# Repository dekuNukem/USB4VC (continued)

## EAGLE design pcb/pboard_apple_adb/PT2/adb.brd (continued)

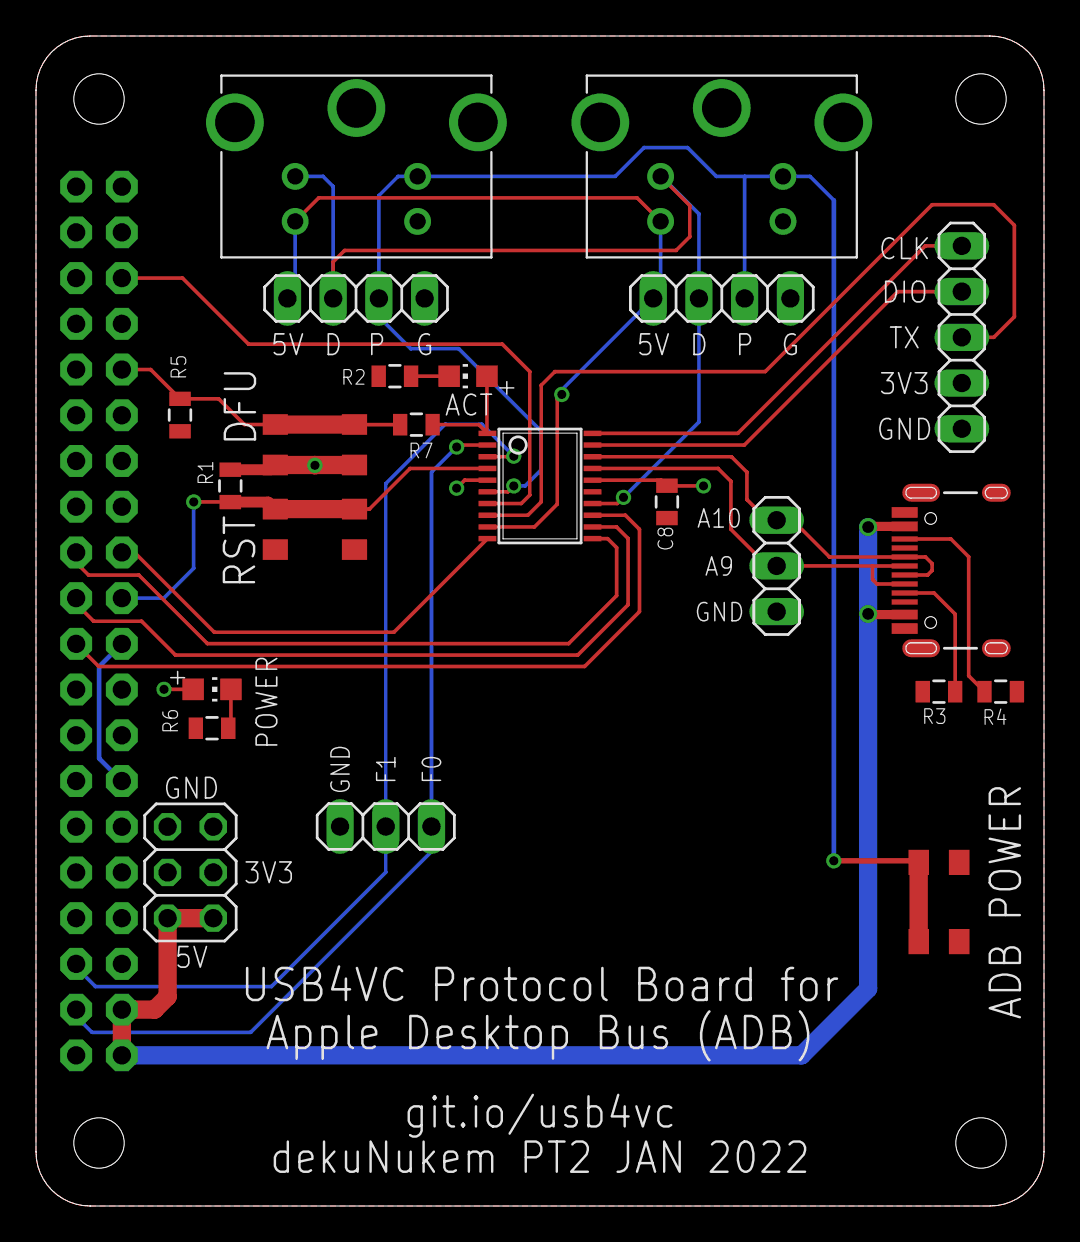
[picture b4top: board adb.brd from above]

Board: 2 copper layers, 56.0 x 65.0 mm, 28 parts (1 on the bottom side), 25 nets.

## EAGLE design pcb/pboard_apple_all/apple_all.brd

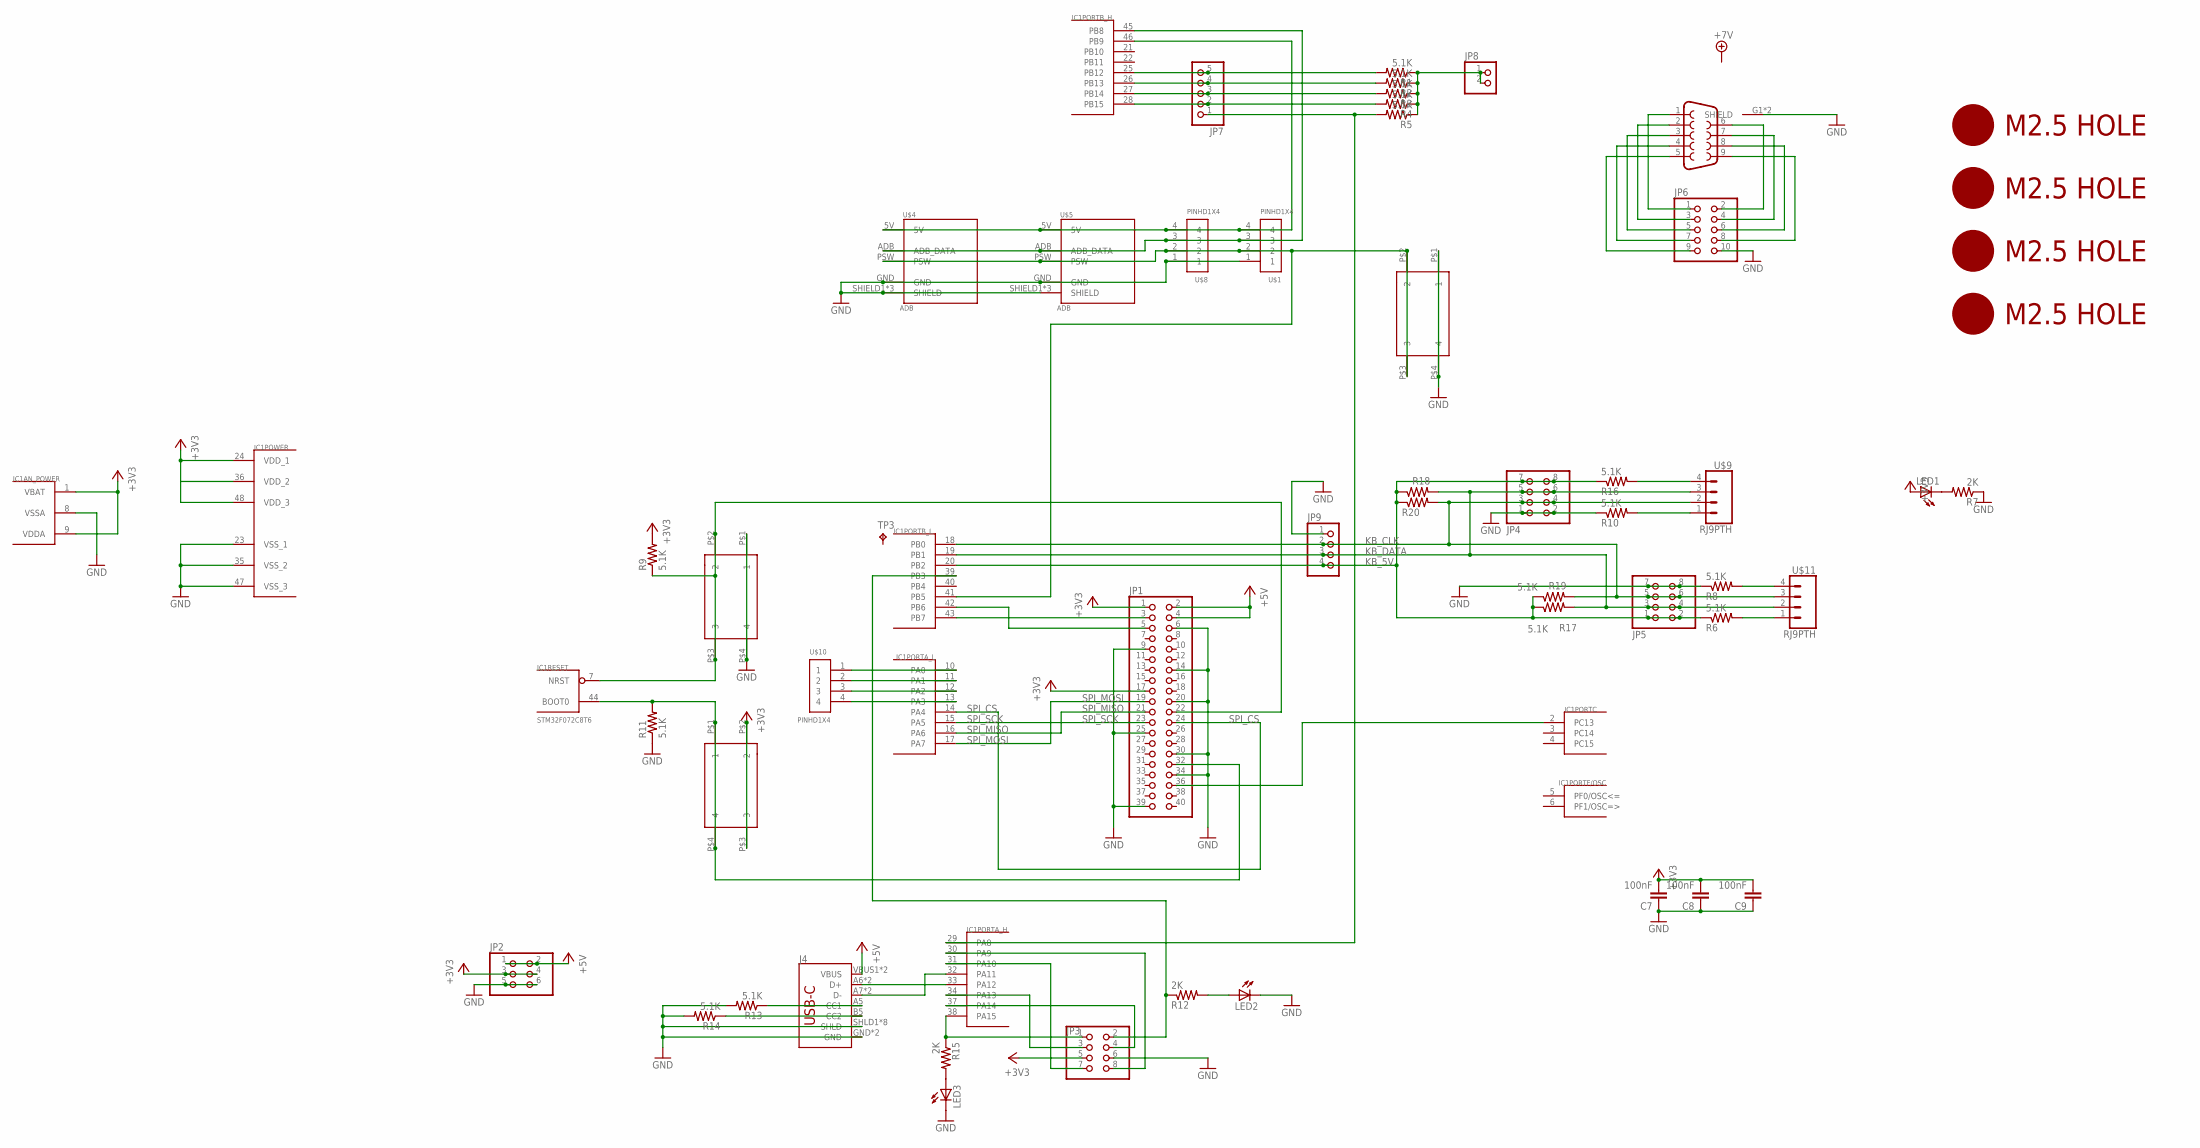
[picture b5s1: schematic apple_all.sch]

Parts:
C7, C8, C9: 100nF; 0805@1
IC1: STM32F072C8T6; TQFP48
J2: DB9FEMALE; DB9
J4: USB_C16PIN; USB-C-16P
JP1: PINHD-2X20-BIG; 2X20-BIG
JP2: PINHD-2X3; 2X03
JP3, JP4, JP5: PINHD-2X4; 2X04
JP6: PINHD-2X5; 2X05
JP7: PINHD-1X5; 1X05
JP8: PINHD-1X2; 1X02
JP9: PINHD-1X4; 1X04
LED1, LED2, LED3: LEDCHIP-LED0805; CHIP-LED0805
R1, R2, R3, R4, R5, R6, R8, R9, R10, R11, R13, R14, R16, R17, R18, R19, R20: 5.1K; 0805
R7, R12, R15: 2K; 0805
SW1, SW2, SW3: 324_SW; 342_SWICH_FOOT
TP3: TPTP12R; TP12R
U$1, U$8, U$10: PINHD1X4; 1X04-CLEANBIG
U$2, U$3, U$6, U$7: M2.5HOLE
U$4, U$5: ADB; DIN4
U$9, U$11: RJ9PTH; RJ9

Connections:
+3V3: C7.2, C8.2, C9.2, IC1.1 (VBAT), IC1.9 (VDDA), IC1.24 (VDD_1), IC1.36 (VDD_2), IC1.48 (VDD_3), JP1.1, JP1.17, JP2.3, JP2.4, JP3.5, LED1.A, R9.2, SW2.P$2 (2), SW2.P$3 (3)
+5V: J4.VBUS1 (VBUS), J4.VBUS2 (VBUS), JP1.2, JP1.4, JP2.1, JP2.2
GND: C7.1, C8.1, C9.1, IC1.8 (VSSA), IC1.23 (VSS_1), IC1.35 (VSS_2), IC1.47 (VSS_3), J2.G1 (SHIELD), J2.G2 (SHIELD), J4.GND, J4.GND2 (GND), J4.SHLD1 (SHLD), J4.SHLD2 (SHLD), J4.SHLD3 (SHLD), J4.SHLD4 (SHLD), J4.SHLD5 (SHLD), J4.SHLD6 (SHLD), J4.SHLD7 (SHLD), J4.SHLD8 (SHLD), JP1.6, JP1.9, JP1.14, JP1.20, JP1.25, JP1.30, JP1.34, JP1.39, JP2.5, JP2.6, JP3.6, JP4.1, JP4.2, JP5.7, JP5.8, JP6.10, JP9.1, LED2.C, LED3.C, R7.1, R8.1, R10.1, R11.1, R13.2, R14.2, SW1.P$1 (1), SW1.P$4 (4), SW3.P$1 (1), SW3.P$4 (4), U$1.1, U$4.GND, U$4.SHIELD1 (SHIELD), U$4.SHIELD2 (SHIELD), U$4.SHIELD3 (SHIELD), U$5.GND, U$5.SHIELD1 (SHIELD), U$5.SHIELD2 (SHIELD), U$5.SHIELD3 (SHIELD), U$8.1
KB_5V: IC1.20 (PB2), JP4.7, JP4.8, JP5.1, JP5.2, JP9.4, R6.1, R16.1, R17.1, R18.1, R19.1, R20.1
KB_CLK: IC1.18 (PB0), JP4.3, JP4.4, JP5.5, JP5.6, JP9.2, R19.2, R20.2, U$9.2, U$11.3
KB_DATA: IC1.19 (PB1), JP4.5, JP4.6, JP5.3, JP5.4, JP9.3, R17.2, R18.2, U$9.3, U$11.2
unnamed: J4.A5 (CC1), R13.1
unnamed: LED2.A, R12.2
unnamed: IC1.46 (PB9), U$1.4, U$4.5V, U$5.5V, U$8.4
unnamed: IC1.28 (PB15), JP7.2, R4.2
unnamed: R8.2, U$11.4
unnamed: IC1.39 (PB3), JP3.2, R12.1
unnamed: J4.B5 (CC2), R14.1
unnamed: IC1.33 (PA12), J4.A6 (D+), J4.B6 (D+)
unnamed: IC1.32 (PA11), J4.A7 (D-), J4.B7 (D-)
unnamed: IC1.27 (PB14), JP7.3, R3.2
unnamed: IC1.31 (PA10), JP3.7
unnamed: IC1.7 (NRST), JP1.22, R9.1, SW1.P$2 (2), SW1.P$3 (3)
unnamed: IC1.30 (PA9), JP3.8
unnamed: IC1.34 (PA13), JP3.3
unnamed: IC1.37 (PA14), JP3.4
unnamed: IC1.44 (BOOT0), JP1.32, R11.2, SW2.P$1 (1), SW2.P$4 (4)
unnamed: IC1.42 (PB6), JP1.5
unnamed: IC1.43 (PB7), JP1.3
unnamed: J2.1, JP6.1
unnamed: IC1.38 (PA15), JP3.1, R15.1
unnamed: LED3.A, R15.2
unnamed: LED1.C, R7.2
unnamed: J2.2, JP6.3
unnamed: J2.3, JP6.5
unnamed: J2.4, JP6.7
unnamed: J2.5, JP6.9
unnamed: J2.6, JP6.2
unnamed: J2.7, JP6.4
unnamed: J2.8, JP6.6
unnamed: IC1.2 (PC13), JP1.36
unnamed: IC1.10 (PA0), U$10.1
unnamed: IC1.11 (PA1), U$10.2
unnamed: IC1.12 (PA2), U$10.3
unnamed: IC1.13 (PA3), U$10.4
unnamed: J2.9, JP6.8
unnamed: IC1.45 (PB8), U$1.3, U$4.ADB (ADB_DATA), U$5.ADB (ADB_DATA), U$8.3
unnamed: IC1.26 (PB13), JP7.4, R2.2
unnamed: IC1.41 (PB5), SW3.P$2 (2), SW3.P$3 (3), U$1.2, U$4.PSW, U$5.PSW, U$8.2
unnamed: IC1.25 (PB12), JP7.5, R1.2
unnamed: IC1.29 (PA8), JP7.1, R5.2
unnamed: JP8.1, JP8.2, R1.1, R2.1, R3.1, R4.1, R5.1
unnamed: R6.2, U$11.1
unnamed: R16.2, U$9.4
unnamed: R10.2, U$9.1
SPI_CS: IC1.14 (PA4), JP1.24
SPI_MISO: IC1.16 (PA6), JP1.21
SPI_MOSI: IC1.17 (PA7), JP1.19
SPI_SCK: IC1.15 (PA5), JP1.23

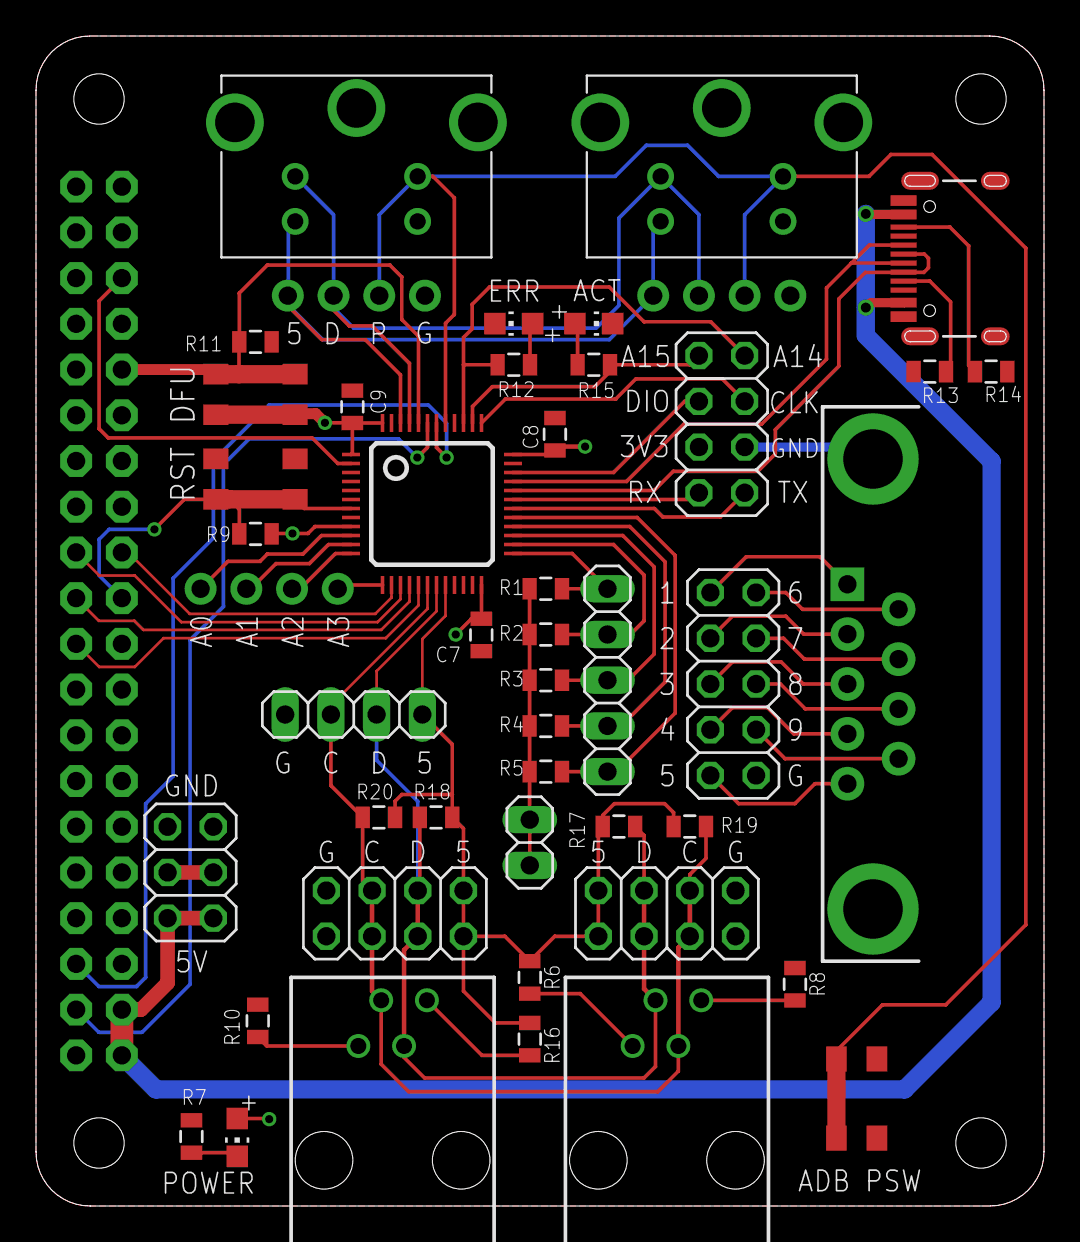
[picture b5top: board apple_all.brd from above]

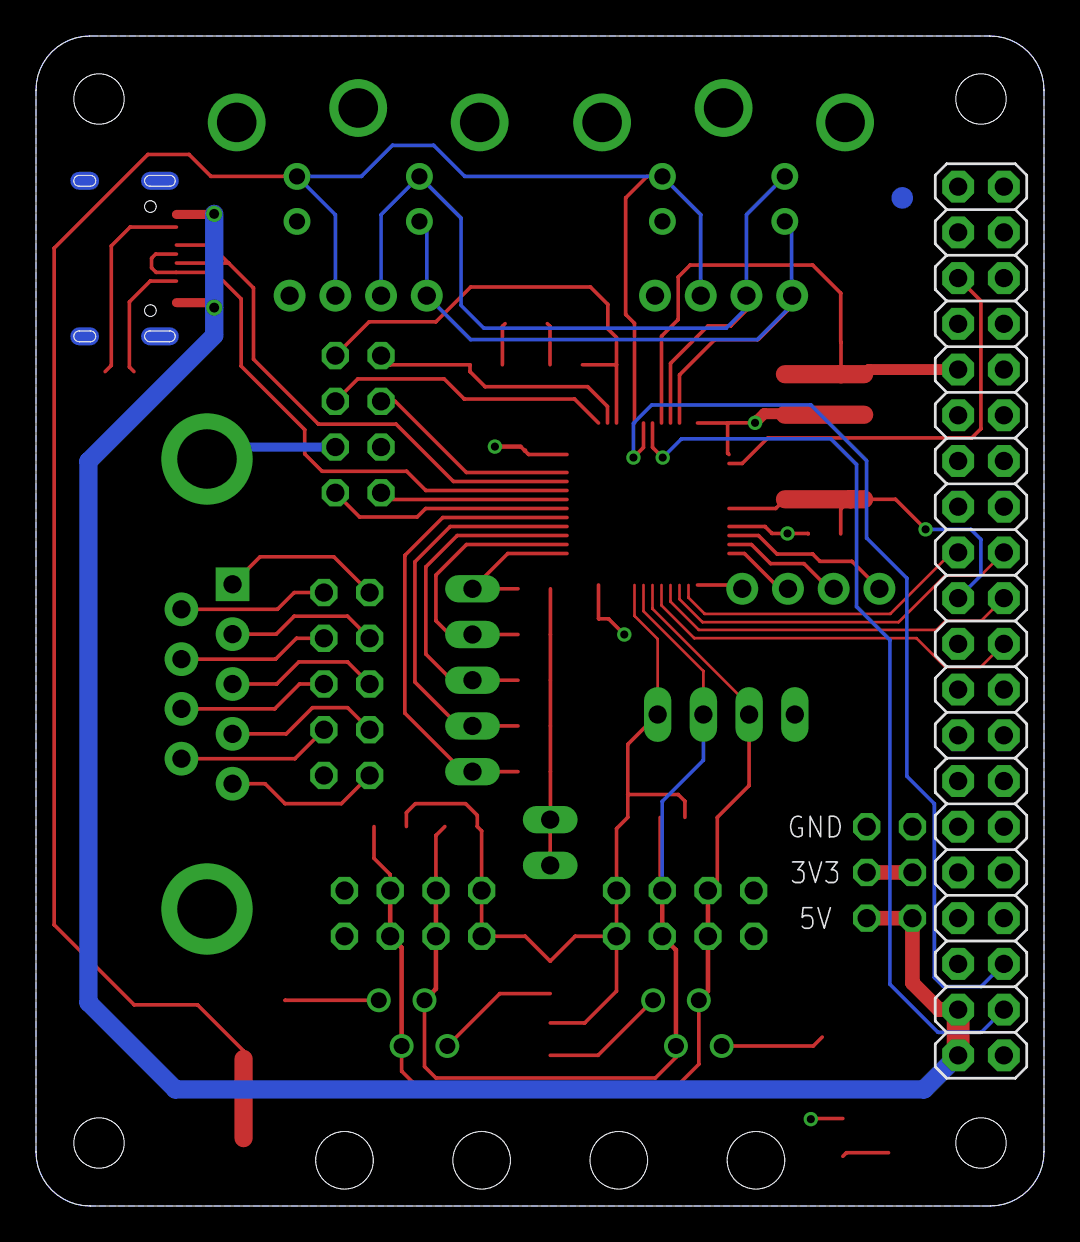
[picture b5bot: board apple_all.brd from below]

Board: 2 copper layers, 56.0 x 65.0 mm, 53 parts (2 on the bottom side), 54 nets.
